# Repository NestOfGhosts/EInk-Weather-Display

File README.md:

# WeaStat
### Is probably what im going to call it ignore the repo name 
Dear reviewers, current readme is prototype. When I build the project irl most photos will be replaced, instructions may become more specific/helpful, and this message will be removed.

## Premise
A pcb with an eink display that shows outside temperatures with a free weather api, and shows inside temperatures with a bme280. All powered with a 18650 battery, attempting to minimize battery drain.

Made by me, for Hack Club Half Life

## BOM

[BOM.csv](https://github.com/NestOfGhosts/EInk-Weather-Display/blob/main/BOM.csv) is only a table of items I personally needed to purchase, not including things I already have. Below is the proper list of materials

|Thing You Need|Details|
|---|---|
|Soldering Equipment|and the expertise to use it. All soldering done for this project should only be through hole|
|Esp32|The Pcb is assuming a DOIT ESP32 DEVKIT V1, and im using a clone|
|18650 Battery & Battery holder|Only necessary if you plan on using a battery to power it. You can use the usb port to power it instead. *More details abt holder below|
|Eink Display|Pcb is assuming a WeAct 2.9"|
|BME280|Pcb is assuming a 6 pin bme, but you could get away with a 4 pin, utilizing the 4 leftmost holes|
|Any 2 buttons|Pcb is assuming a 5 pin mx cherry compatible keyboard switch|

*If you want to use a battery, either use a normal battery holder and an 1N4007 diode to slightly lower the voltage(needed bc full battery outputs more than 3.6v), or a dedicated module that controls 3v3 output ([example](https://www.aliexpress.com/item/1005006351276180.html?spm=a2g0o.detail.0.0.2164unO6unO65w&mp=1&pdp_npi=6%40dis%21CAD%21CAD+4.67%21CAD+4.67%21%21CAD+4.67%21%21%21%4021030f8317938421479141980e0f47%2112000046129008872%21ct%21CA%216330886401%21%211%210%21)). Alternatively, you can use another battery source that consistantly outputs ~3.3v

If you have different parts than the pcb assumes, you can edit the [.kicad_pcb file](https://github.com/NestOfGhosts/EInk-Weather-Display/blob/main/Pcb%20Files/weatstat.kicad_pcb) in KiCad with the footprints of your actual parts.

## Build Steps

### (Optional) Holder

Print holder from [Holder Files](https://github.com/NestOfGhosts/EInk-Weather-Display/tree/main/Holder%20Files) (FCStd is an editable cad file, for freecad. If you want to edit the source you have to use freecad) (STL for 3d printing)

### Firmware
#### Instructions for windows. Figure out equivalent actions for other OSs, and do them :)
1. Download Visual Studio Code, and in VSCode's extensions sidebar install Platformio.
2. Clone the Firmware Files folder, and open it in VSCode (make sure to trust the workspace)
3. Set the esp32 to bootloader mode by resetting it and setting GPIO0 to LOW (grounding gpio0). You may also use any "boot" buttons if your esp32 has it.
4. (Optional) Open "Device Manager" (In windows)

- Expand the "Ports (COM & LPT)" section

- Plug in the esp  

- Take note of any new devices  

5. Click the house button at the bottom. Open the Firmware Files folder from earlier. Then, (with your board plugged in), click on the alien on the sidebar. Click "Build Filesystem", wait for finish, then click upload filesystem image.

6. Wait for it to finish. Finally, click the checkmark at the bottom, then when it completes press the right arrow.

Wow ur done flashing.

### Soldering
#### Hopefully you have a fume extractor
#### Schematic [here](https://github.com/NestOfGhosts/EInk-Weather-Display/blob/main/Pcb%20Files/shematic.pdf). U1 is esp, J2 is display, J3 is the BME, the switches are the buttons, and the battery is the battery (technically the holder but whtever)
1. Solder ESP to backside
2. Rest of things to frontside.
- The battery holder doesnt have a spot on the pcb, but the holder has a bit of extra space for it so if you're using the holder you can just kinda pit it next to it
- In terms of soldering, solder the battery holder's 3v3 output to 3v3, and the gnd to gnd. If you're using a basic battery holder put the diode in between the plus side and the esp, with the direction allowing power to flow from the battery to the ESP.
### Use
Make sure there's power
- Press both buttons at the same time to turn on config mode
- Use a device to connect to the new hotspot that is created by the esp. Named "E-Ink Weather"
- While connected to the hotspot, go on a browser and go to 192.168.4.1
- You can now change location (In WGS84 coordinates. Look them up with a maps app, if you're not sure if its WGS84 use a converter), and what each screen looks like.
### Customizability 
- Code customized by copying the firmware folder (INSERT LINK TO FOLDER), opening in [VS Code](https://code.visualstudio.com/download), and using platformio to compile/build.
- Case customized with [.FCStd](https://github.com/NestOfGhosts/EInk-Weather-Display/blob/main/Holder%20Files/halvedLife.FCStd) or [.step](https://github.com/NestOfGhosts/EInk-Weather-Display/blob/main/Holder%20Files/halvedLife-Body.step)
- Pcb customized using [kicad_pcb](https://github.com/NestOfGhosts/EInk-Weather-Display/blob/main/Pcb%20Files/weatstat.kicad_pcb) (using kicad obv)
-

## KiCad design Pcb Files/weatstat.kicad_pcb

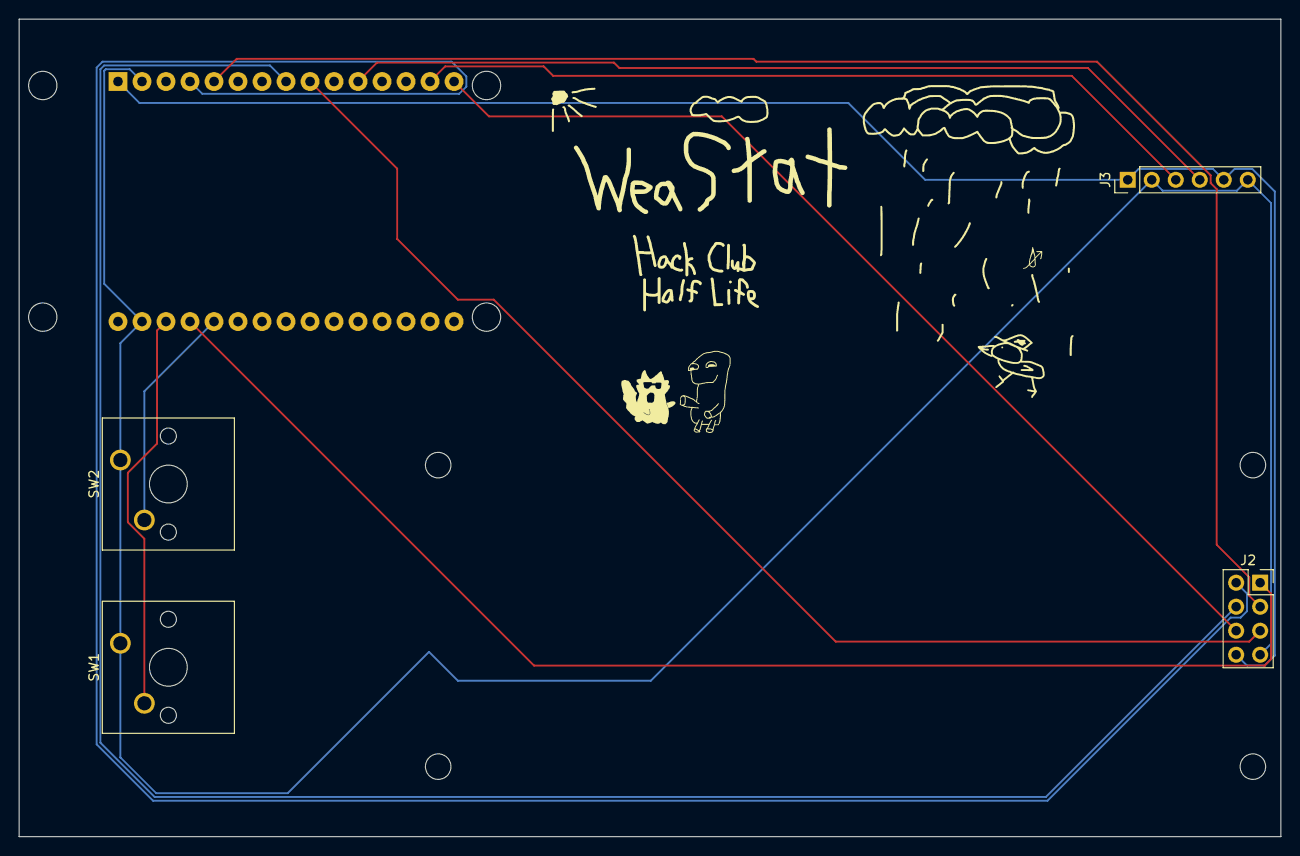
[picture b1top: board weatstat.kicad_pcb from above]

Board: 2 copper layers, 133.5 x 86.5 mm, 5 parts (1 on the bottom side), 12 nets.

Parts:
J2: Conn_02x04_Odd_Even; PinHeader_2x04_P2.54mm_Vertical
J3: Conn_01x06; PinHeader_1x06_P2.54mm_Vertical
SW1, SW2: SW_Push; SW_Cherry_MX_1.00u_PCB
U1: ESP32-DEVKIT-V1; MODULE_ESP32_DEVKIT_V1

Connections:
+3V3: J2.8, J3.1, J3.5, U1.1 (3V3)
/BMESCL: J3.3, U1.14 (D22)
/BMESDA: J3.4, U1.11 (D21)
/BUSY: J2.1, U1.27 (D12)
/CS: J2.4, U1.8 (D5)
/ChangeMode: SW2.2, U1.26 (D14)
/DC: J2.3, U1.5 (D4)
/RST: J2.2, U1.4 (D2)
/Refresh: SW1.2, U1.28 (D13)
/SCL: J2.5, U1.9 (D18)
/SDA: J2.6, U1.15 (D23)
GND: J2.7, J3.2, J3.6, SW1.1, SW2.1, U1.2 (GND), U1.29 (GND)
